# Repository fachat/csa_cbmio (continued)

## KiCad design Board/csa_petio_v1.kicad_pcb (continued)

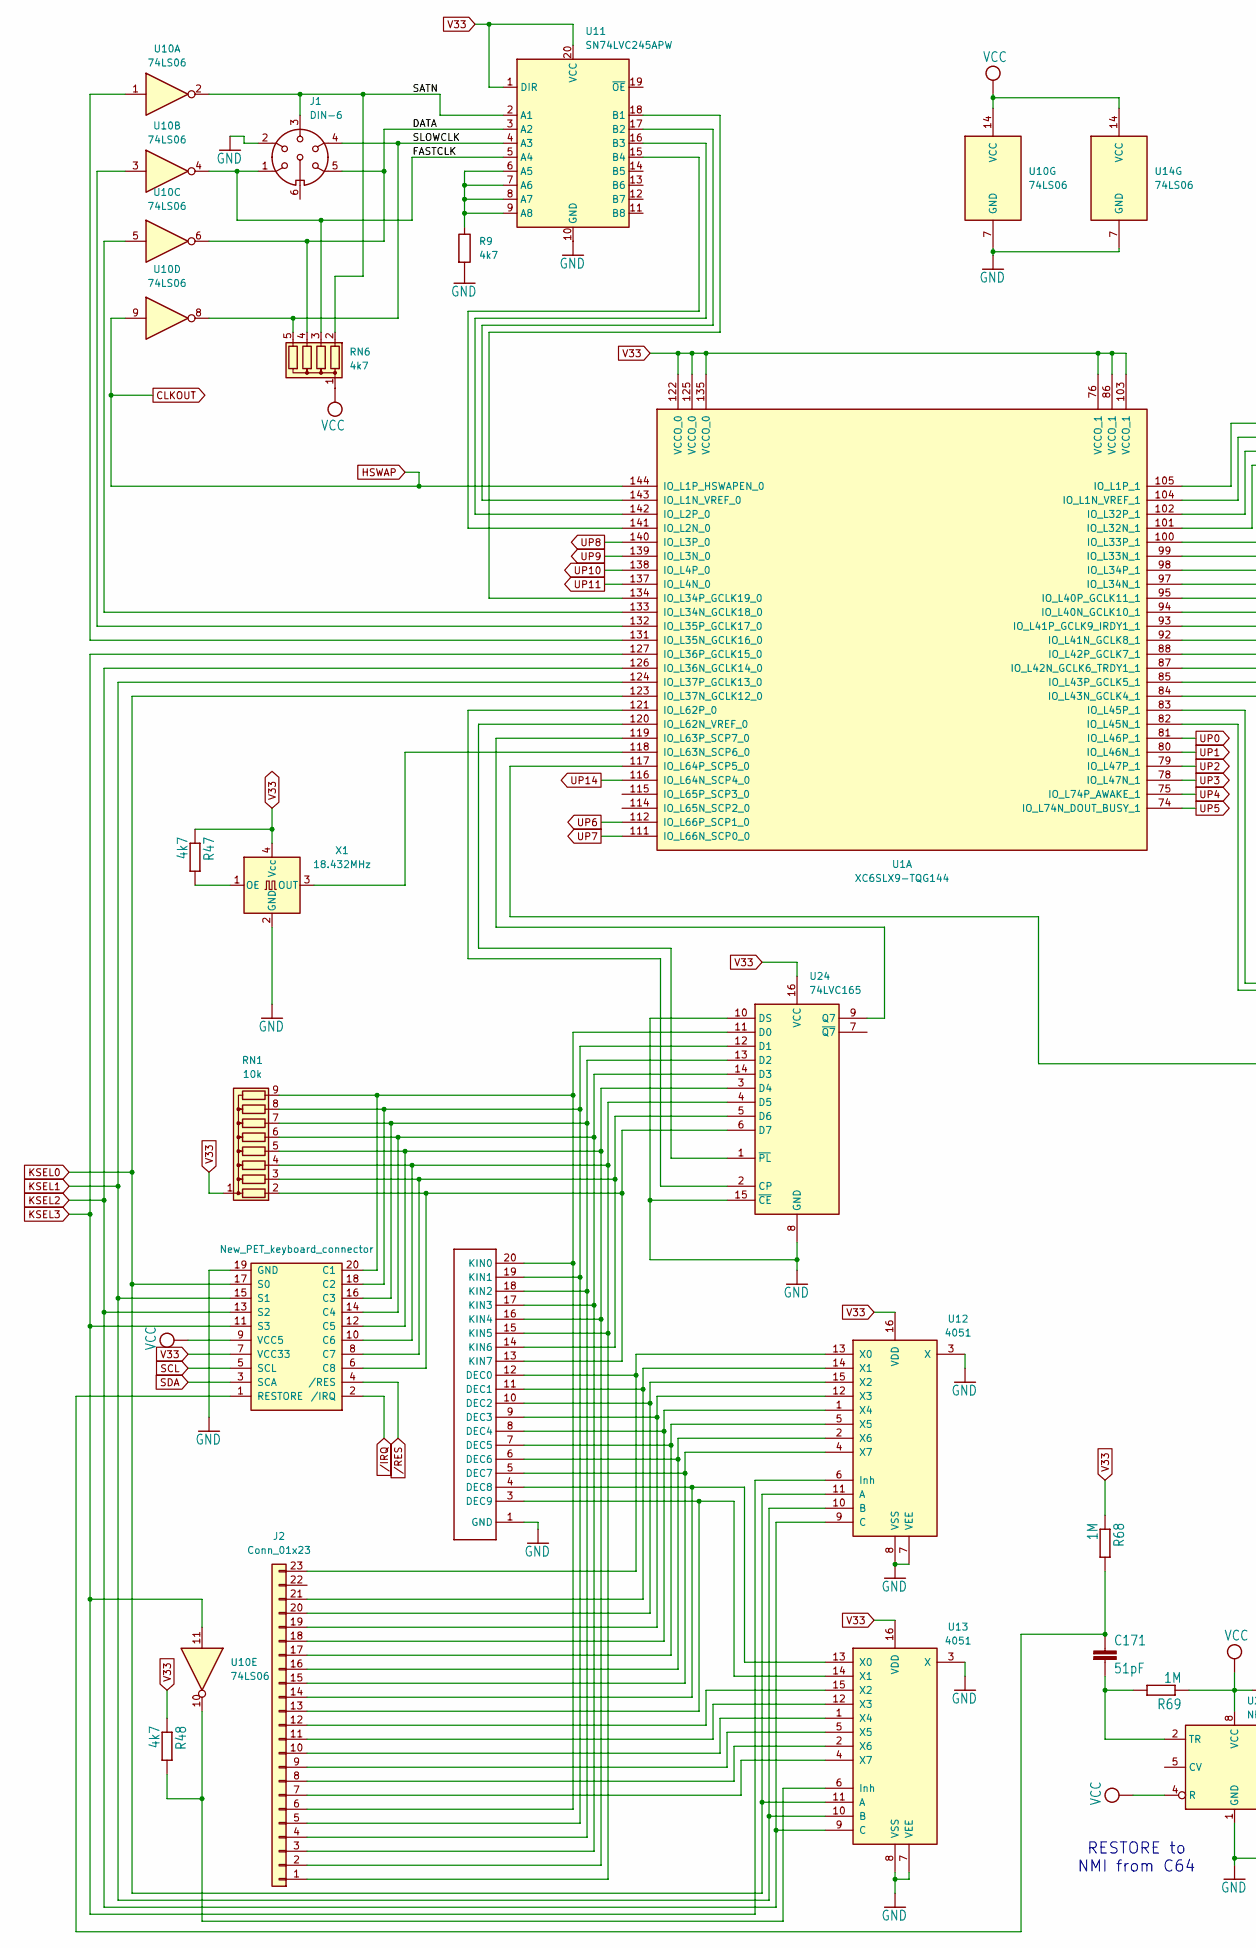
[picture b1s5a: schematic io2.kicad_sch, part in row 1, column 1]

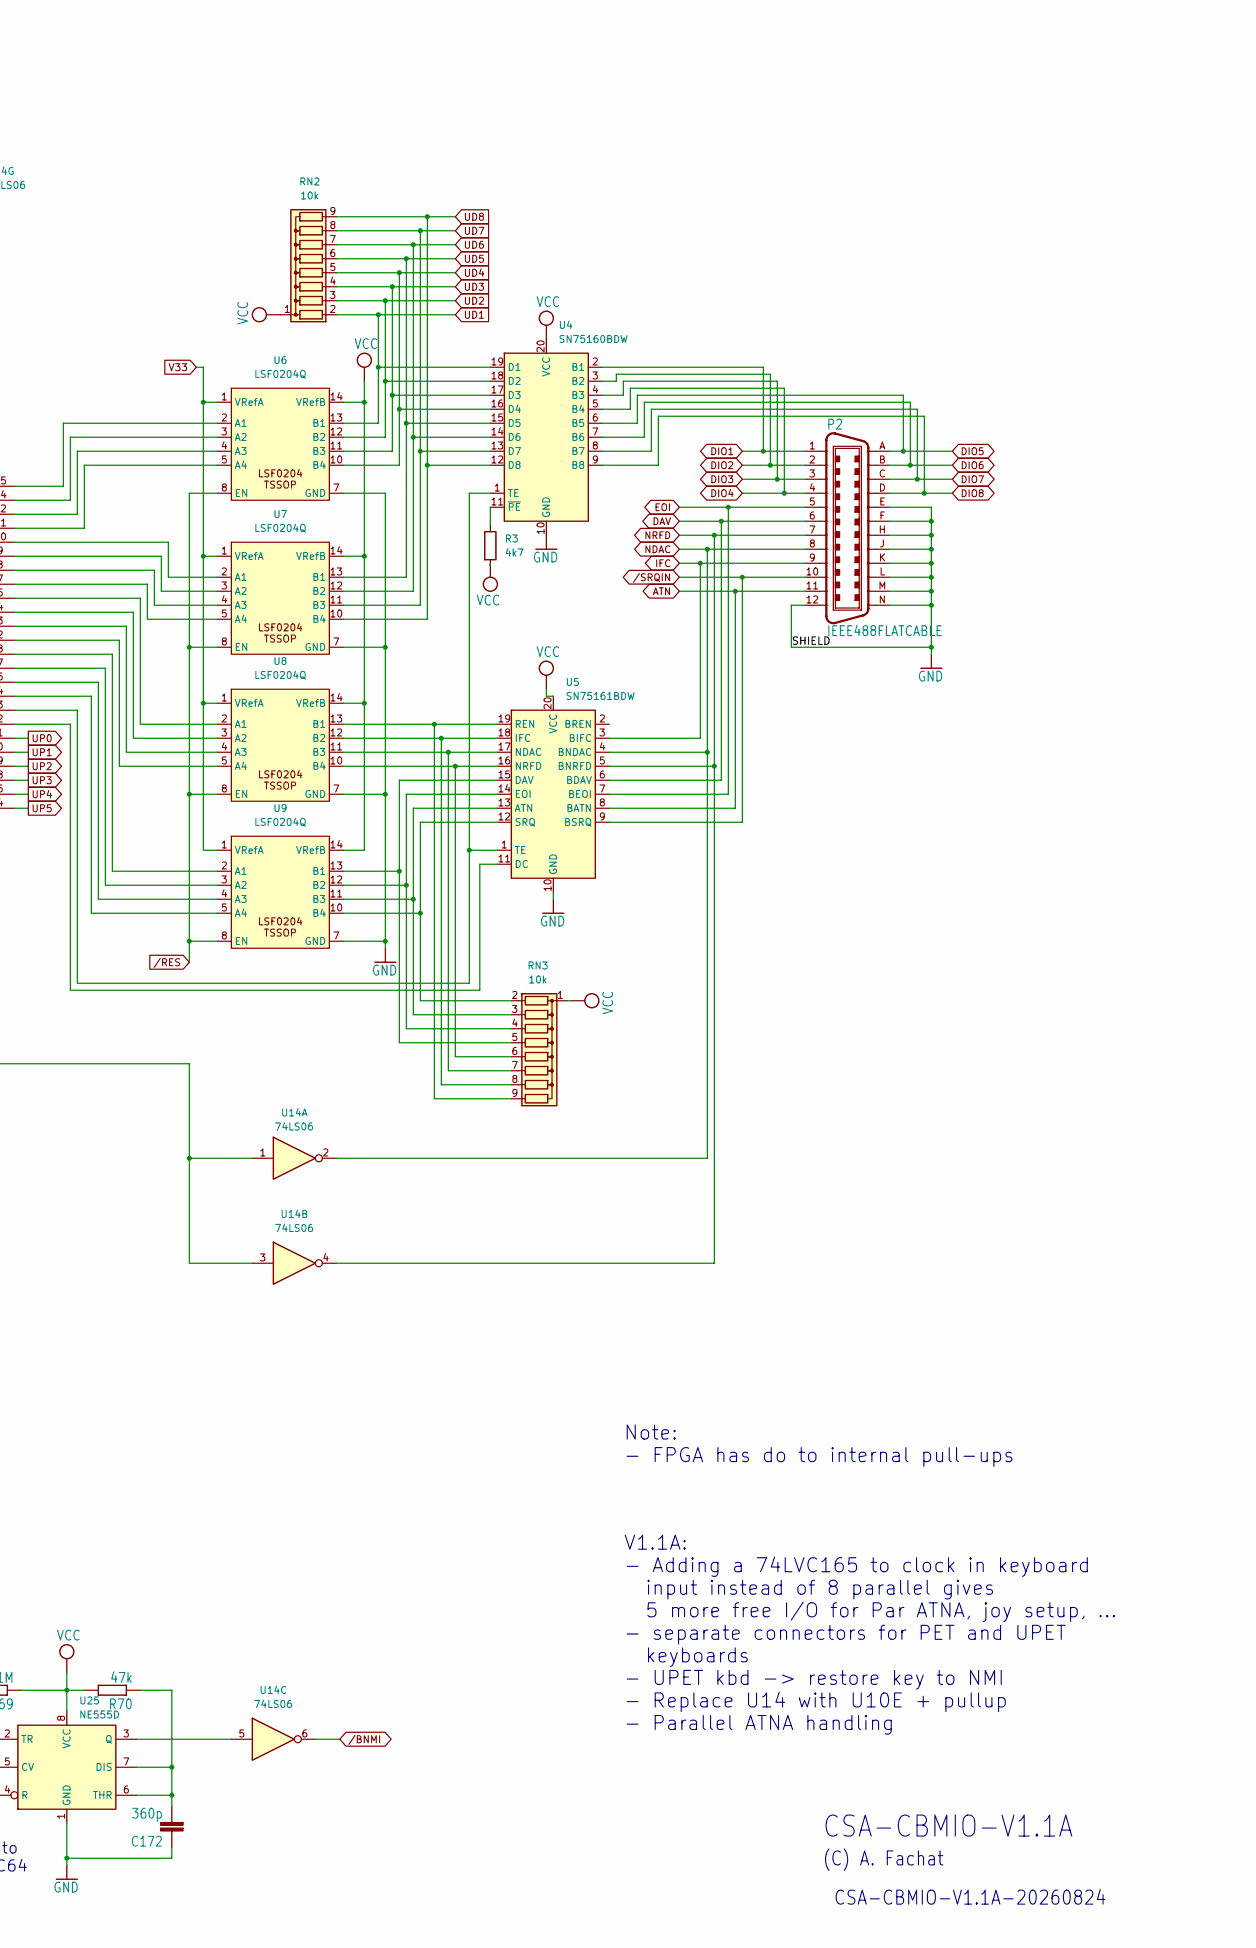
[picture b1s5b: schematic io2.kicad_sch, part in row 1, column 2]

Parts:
C171: 51pF; C_0805_2012Metric
C172: 360p; C_0805_2012Metric
J1: DIN-6; DIN6PIEC
J2: Conn_01x23; PinSocket_1x23_P2.54mm_Vertical
J3: New_PET_keyboard_connector; IDC-Header_2x10_P2.54mm_Vertical
P2: IEEE488FLATCABLE; FLAT24_IDC
P8: PinHeader_1x20_P2.54mm_Vertical
R3, R9, R47, R48: 4k7; R_0603_1608Metric_Pad0.98x0.95mm_HandSolder
R68, R69: 1M; R_0603_1608Metric_Pad0.98x0.95mm_HandSolder
R70: 47k; R_0603_1608Metric_Pad0.98x0.95mm_HandSolder
RN1, RN2, RN3: 10k; R_Array_SIP9
RN6: 4k7; R_Array_SIP5
U1: XC6SLX9-TQG144; TQFP-144_20x20mm_P0.5mm
U4: SN75160BDW; SOIC-20W_7.5x12.8mm_P1.27mm
U5: SN75161BDW; SOIC-20W_7.5x12.8mm_P1.27mm
U6, U7, U8, U9: LSF0204Q; TSSOP-14_4.4x5mm_P0.65mm
U10, U14: 74LS06; SO-14_3.9x8.65mm_P1.27mm
U11: SN74LVC245APW; TSSOP-20_4.4x6.5mm_P0.65mm
U12, U13: 4051; SOP-16_3.9x9.9mm_P1.27mm
U24: 74LVC165; TSSOP-16_4.4x5mm_P0.65mm
U25: NE555D; SOIC-8_3.9x4.9mm_P1.27mm
X1: 18.432MHz; Oscillator_SMD_SeikoEpson_SG8002CE-4Pin_3.2x2.5mm; LCSC C7434931

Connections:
/IO2/DATA: J1.5, RN6.4 (R3), U10.6, U11.3 (A2)
/IO2/FASTCLK: J1.1, RN6.3 (R2), U10.4, U11.5 (A4)
/IO2/SATN: J1.3, RN6.2 (R1), U10.2, U11.2 (A1)
/IO2/SLOWCLK: J1.4, RN6.5 (R4), U10.8, U11.4 (A3)
ATN: P2.11, U5.8 (BATN)
CLKOUT: U1.144 (IO_L1P_HSWAPEN_0), U10.9; also elsewhere on the board
DAV: P2.6, U5.6 (BDAV)
DIO1: P2.1, U4.2 (B1)
DIO2: P2.2, U4.3 (B2)
DIO3: P2.3, U4.4 (B3)
DIO4: P2.4, U4.5 (B4)
DIO5: P2.A (13), U4.6 (B5)
DIO6: P2.B (14), U4.7 (B6)
DIO7: P2.C (15), U4.8 (B7)
DIO8: P2.D (16), U4.9 (B8)
EOI: P2.5, U5.7 (BEOI); also elsewhere on the board
GND: C172.1, J1.2, J3.19 (GND), P2.12, P2.E (17), P2.F (18), P2.H (19), P2.J (20), P2.K (21), P2.L (22), P2.M (23), P2.N (24), P8.1 (GND), R9.2, U4.10 (GND), U5.10 (GND), U6.7 (GND), U7.7 (GND), U8.7 (GND), U9.7 (GND), U10.7 (GND), U11.10 (GND), U12.3 (X), U12.7 (VEE), U12.8 (VSS), U13.3 (X), U13.7 (VEE), U13.8 (VSS), U14.7 (GND), U24.8 (GND), U24.10 (DS), U24.15 (~CE), U25.1 (GND), X1.2 (GND); also elsewhere on the board
IFC: P2.9, U5.3 (BIFC)
KSEL0: J3.17 (S0), U1.123 (IO_L37N_GCLK12_0), U12.11 (A), U13.11 (A)
KSEL1: J3.15 (S1), U1.124 (IO_L37P_GCLK13_0), U12.10 (B), U13.10 (B)
KSEL2: J3.13 (S2), U1.126 (IO_L36N_GCLK14_0), U12.9 (C), U13.9 (C)
KSEL3: J3.11 (S3), U1.127 (IO_L36P_GCLK15_0), U10.11, U12.6 (Inh)
NDAC: P2.8, U5.4 (BNDAC), U14.2
NRFD: P2.7, U5.5 (BNRFD), U14.4
unnamed: J2.1, J3.10 (C6), P8.15 (KIN5), RN1.4 (R3), U24.4 (D5)
unnamed: J2.2, J3.12 (C5), P8.16 (KIN4), RN1.5 (R4), U24.3 (D4)
unnamed: J2.3, J3.14 (C4), P8.17 (KIN3), RN1.6 (R5), U24.14 (D3)
unnamed: J2.4, J3.16 (C3), P8.18 (KIN2), RN1.7 (R6), U24.13 (D2)
unnamed: J2.5, J3.18 (C2), P8.19 (KIN1), RN1.8 (R7), U24.12 (D1)
unnamed: J2.6, J3.20 (C1), P8.20 (KIN0), RN1.9 (R8), U24.11 (D0)
unnamed: J2.7, U13.4 (X7)
unnamed: J2.8, U13.2 (X6)
unnamed: J2.9, U13.5 (X5)
unnamed: J2.10, U13.1 (X4)
unnamed: J2.11, U13.12 (X3)
unnamed: J2.12, U13.15 (X2)
unnamed: J2.13, P8.3 (DEC9), U13.14 (X1)
unnamed: J2.14, P8.4 (DEC8), U13.13 (X0)
unnamed: J2.15, P8.5 (DEC7), U12.4 (X7)
unnamed: J2.16, P8.6 (DEC6), U12.2 (X6)
unnamed: J2.17, P8.7 (DEC5), U12.5 (X5)
unnamed: J2.18, P8.8 (DEC4), U12.1 (X4)
unnamed: J2.19, P8.9 (DEC3), U12.12 (X3)
unnamed: J2.20, P8.10 (DEC2), U12.15 (X2)
unnamed: J2.21, P8.11 (DEC1), U12.14 (X1)
unnamed: J2.23, P8.12 (DEC0), U12.13 (X0)
unnamed: J3.8 (C7), P8.14 (KIN6), RN1.3 (R2), U24.5 (D6)
unnamed: J3.6 (C8), P8.13 (KIN7), RN1.2 (R1), U24.6 (D7)
unnamed: C171.1, J3.1 (RESTORE), R68.2
unnamed: RN3.2 (R1), U5.12 (SRQ), U9.10 (B4)
unnamed: RN3.3 (R2), U5.13 (ATN), U9.11 (B3)
unnamed: RN3.4 (R3), U5.14 (EOI), U9.12 (B2)
unnamed: RN3.5 (R4), U5.15 (DAV), U9.13 (B1)
unnamed: RN3.6 (R5), U5.16 (NRFD), U8.10 (B4)
unnamed: RN3.7 (R6), U5.17 (NDAC), U8.11 (B3)
unnamed: RN3.8 (R7), U5.18 (IFC), U8.12 (B2)
unnamed: RN3.9 (R8), U5.19 (REN), U8.13 (B1)
unnamed: U1.104 (IO_L1N_VREF_1), U6.3 (A2)
unnamed: U1.105 (IO_L1P_1), U6.2 (A1)
unnamed: U1.101 (IO_L32N_1), U6.5 (A4)
unnamed: U1.102 (IO_L32P_1), U6.4 (A3)
unnamed: U1.99 (IO_L33N_1), U7.3 (A2)
unnamed: U1.100 (IO_L33P_1), U7.2 (A1)
unnamed: U1.97 (IO_L34N_1), U7.5 (A4)
unnamed: U1.133 (IO_L34N_GCLK18_0), U10.5
unnamed: U1.98 (IO_L34P_1), U7.4 (A3)
unnamed: U1.131 (IO_L35N_GCLK16_0), U10.1
unnamed: U1.132 (IO_L35P_GCLK17_0), U10.3
unnamed: U1.94 (IO_L40N_GCLK10_1), U8.3 (A2)
unnamed: U1.95 (IO_L40P_GCLK11_1), U8.2 (A1)
unnamed: U1.92 (IO_L41N_GCLK8_1), U8.5 (A4)
unnamed: U1.93 (IO_L41P_GCLK9_IRDY1_1), U8.4 (A3)
unnamed: U1.87 (IO_L42N_GCLK6_TRDY1_1), U9.3 (A2)
unnamed: U1.88 (IO_L42P_GCLK7_1), U9.2 (A1)
unnamed: U1.84 (IO_L43N_GCLK4_1), U9.5 (A4)
unnamed: U1.85 (IO_L43P_GCLK5_1), U9.4 (A3)
unnamed: U1.82 (IO_L45N_1), U5.11 (DC)
unnamed: U1.83 (IO_L45P_1), U4.1 (TE), U5.1 (TE)
unnamed: U1.120 (IO_L62N_VREF_0), U24.1 (~PL)
unnamed: U1.121 (IO_L62P_0), U24.2 (CP)
unnamed: U1.118 (IO_L63N_SCP6_0), X1.3 (OUT)
unnamed: U1.119 (IO_L63P_SCP7_0), U24.9 (Q7)
unnamed: U1.117 (IO_L64P_SCP5_0), U14.1, U14.3
unnamed: R3.1, U4.11 (~PE)
unnamed: R9.1, U11.6 (A5), U11.7 (A6), U11.8 (A7), U11.9 (A8)
unnamed: U1.134 (IO_L34P_GCLK19_0), U11.18 (B1)
unnamed: U1.143 (IO_L1N_VREF_0), U11.17 (B2)
unnamed: U1.142 (IO_L2P_0), U11.16 (B3)
unnamed: U1.141 (IO_L2N_0), U11.15 (B4)
unnamed: R48.2, U10.10, U13.6 (Inh)
unnamed: C172.2, R70.1, U25.6 (THR), U25.7 (DIS)
unnamed: U14.5, U25.3 (Q)
unnamed: C171.2, R69.2, U25.2 (TR)
unnamed: R47.2, X1.1 (OE)
SCL: J3.5 (SCL)
SDA: J3.3 (SCA)
UD1: RN2.2 (R1), U4.19 (D1), U6.13 (B1); also elsewhere on the board
UD2: RN2.3 (R2), U4.18 (D2), U6.12 (B2); also elsewhere on the board
UD3: RN2.4 (R3), U4.17 (D3), U6.11 (B3); also elsewhere on the board
UD4: RN2.5 (R4), U4.16 (D4), U6.10 (B4); also elsewhere on the board
UD5: RN2.6 (R5), U4.15 (D5), U7.13 (B1); also elsewhere on the board
UD6: RN2.7 (R6), U4.14 (D6), U7.12 (B2); also elsewhere on the board
UD7: RN2.8 (R7), U4.13 (D7), U7.11 (B3); also elsewhere on the board
UD8: RN2.9 (R8), U4.12 (D8), U7.10 (B4); also elsewhere on the board
UP0: U1.81 (IO_L46P_1); also elsewhere on the board
UP1: U1.80 (IO_L46N_1); also elsewhere on the board
UP2: U1.79 (IO_L47P_1); also elsewhere on the board
UP3: U1.78 (IO_L47N_1); also elsewhere on the board
UP4: U1.75 (IO_L74P_AWAKE_1); also elsewhere on the board
UP5: U1.74 (IO_L74N_DOUT_BUSY_1); also elsewhere on the board
UP6: U1.112 (IO_L66P_SCP1_0); also elsewhere on the board
UP7: U1.111 (IO_L66N_SCP0_0); also elsewhere on the board
UP8: U1.140 (IO_L3P_0); also elsewhere on the board
UP9: U1.139 (IO_L3N_0); also elsewhere on the board
UP10: U1.138 (IO_L4P_0); also elsewhere on the board
UP11: U1.137 (IO_L4N_0); also elsewhere on the board
UP14: U1.116 (IO_L64N_SCP4_0); also elsewhere on the board
V33: J3.7 (VCC33), R47.1, R48.1, R68.1, RN1.1 (common), U1.76 (VCCO_1), U1.86 (VCCO_1), U1.103 (VCCO_1), U1.122 (VCCO_0), U1.125 (VCCO_0), U1.135 (VCCO_0), U6.1 (VRefA), U7.1 (VRefA), U8.1 (VRefA), U9.1 (VRefA), U11.1 (DIR), U11.20 (VCC), U12.16 (VDD), U13.16 (VDD), U24.16 (VCC), X1.4 (Vcc); also elsewhere on the board
VCC: J3.9 (VCC5), R3.2, R69.1, R70.2, RN2.1 (common), RN3.1 (common), RN6.1 (common), U4.20 (VCC), U5.20 (VCC), U6.14 (VRefB), U7.14 (VRefB), U8.14 (VRefB), U9.14 (VRefB), U10.14 (VCC), U14.14 (VCC), U25.4 (R), U25.8 (VCC); also elsewhere on the board
/BNMI: U14.6; also elsewhere on the board
/IRQ: J3.2 (/IRQ); also elsewhere on the board
/RES: J3.4 (/RES), U6.8 (EN), U7.8 (EN), U8.8 (EN), U9.8 (EN); also elsewhere on the board

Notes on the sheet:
CSA-CBMIO-V1.1A
Note: - FPGA has do to internal pull-ups
CSA-CBMIO-V1.1A-20260824
RESTORE to NMI from C64
(C) A. Fachat
V1.1A: - Adding a 74LVC165 to clock in keyboard input instead of 8 parallel gives 5 more free I/O for Par ATNA, joy setup, ... - separate connectors for PET and UPET keyboards - UPET kbd -> restore key to NMI - Replace U14 with U10E + pullup - Parallel ATNA handling

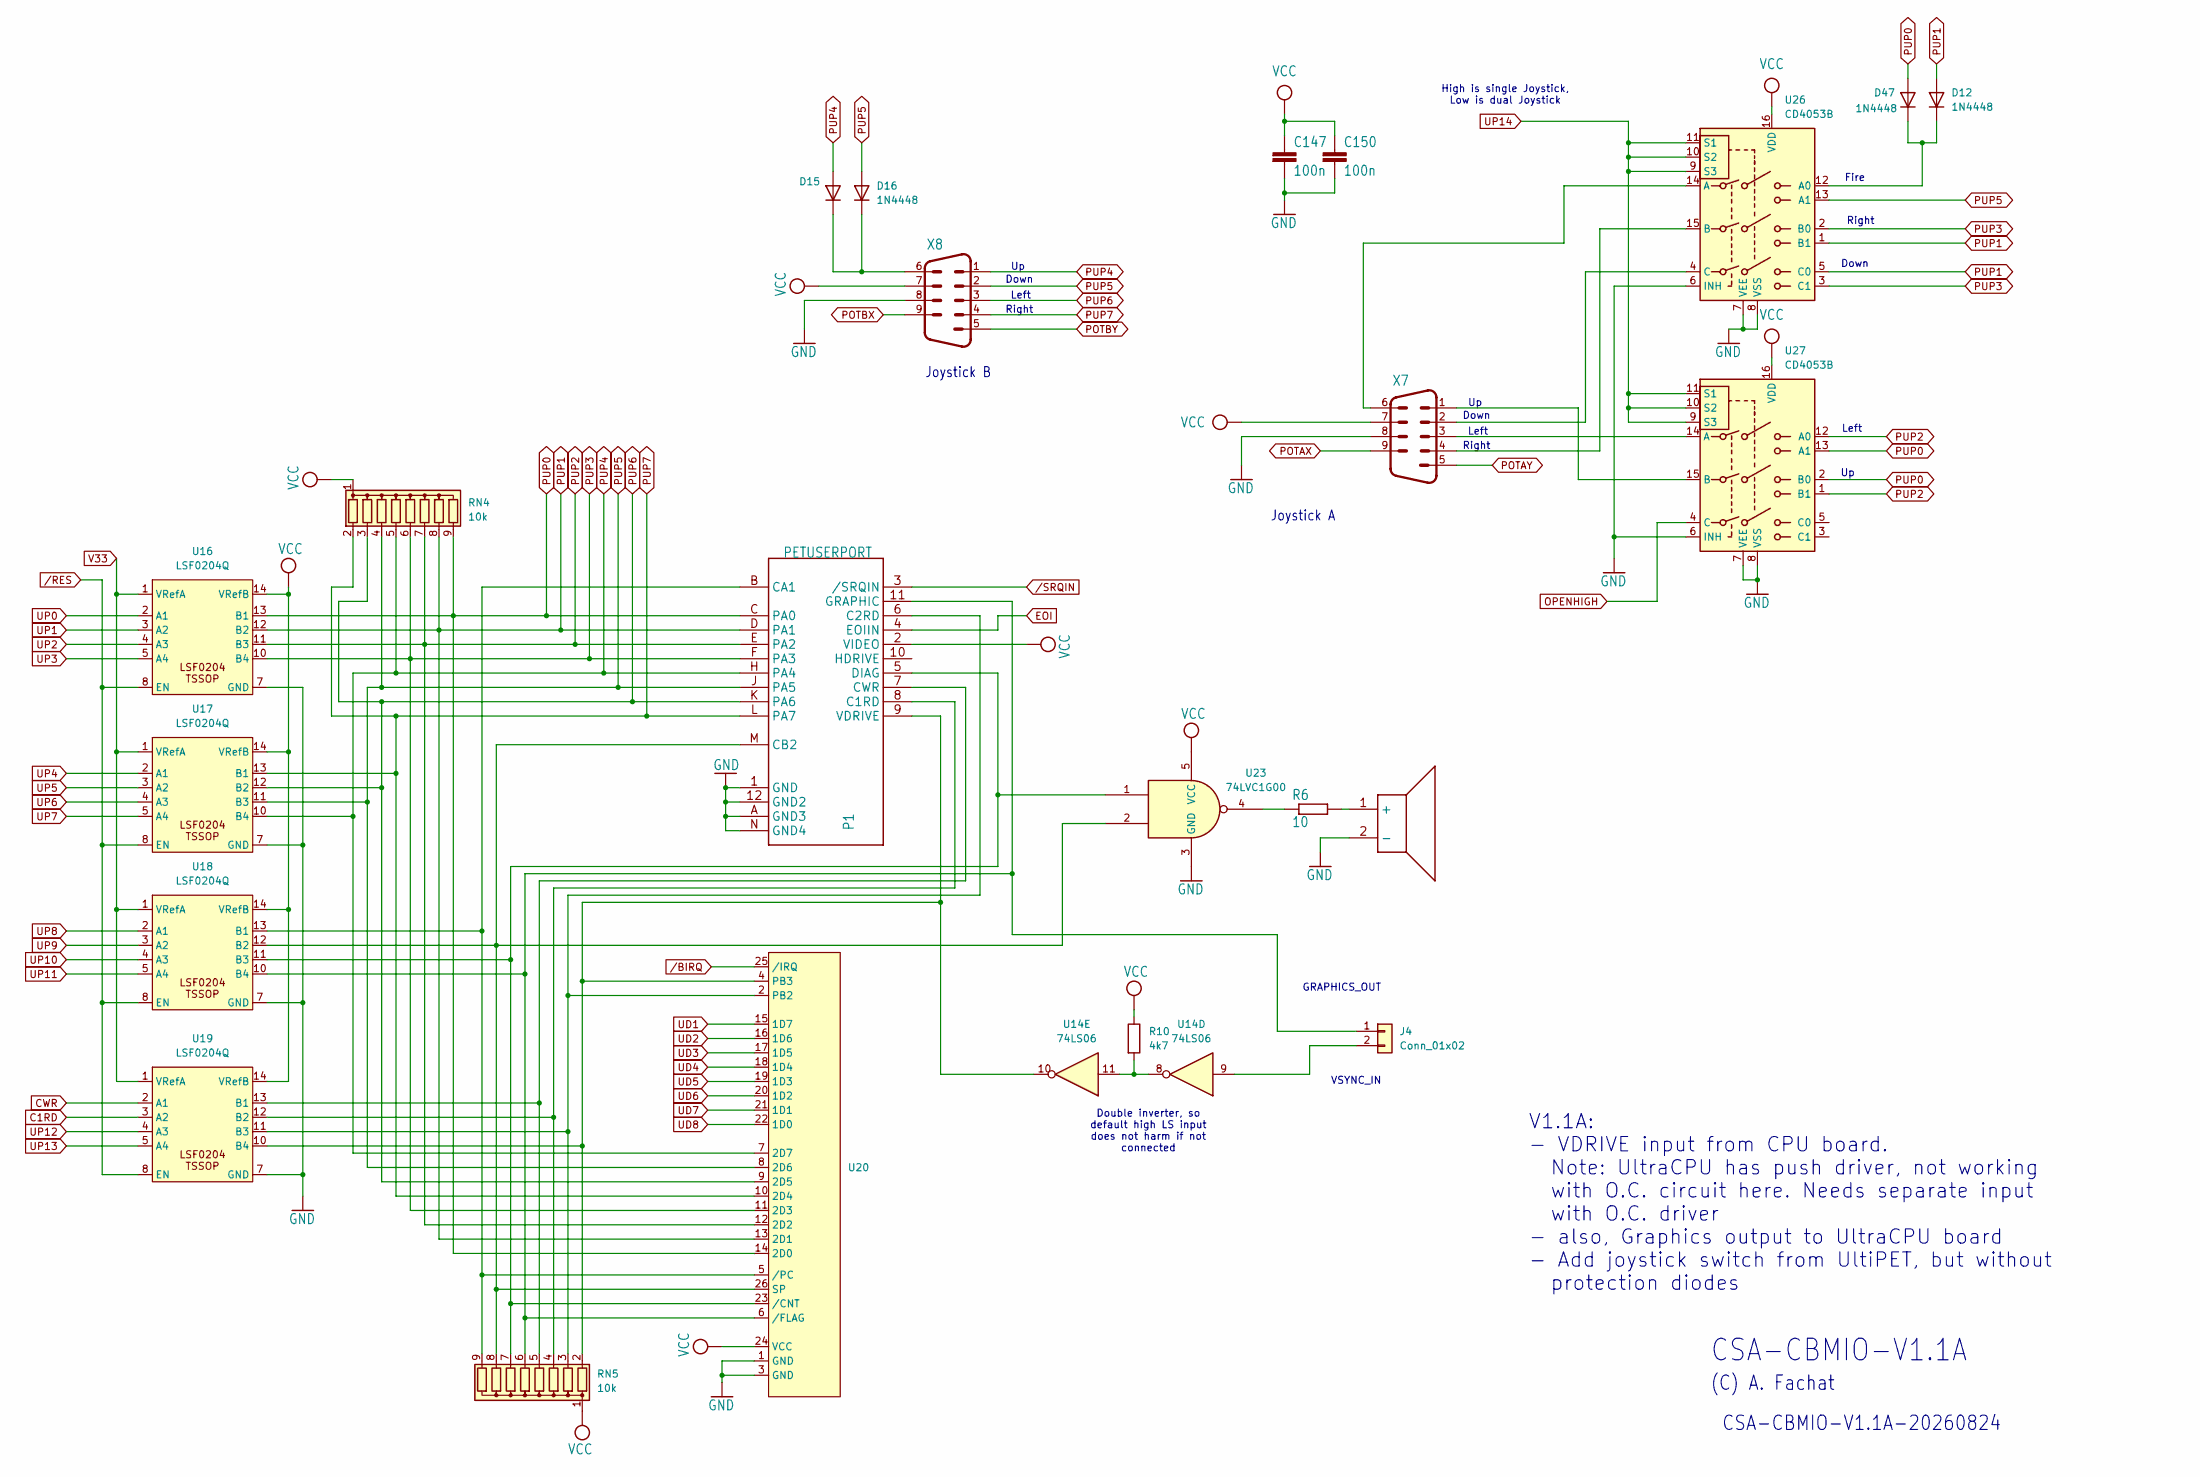
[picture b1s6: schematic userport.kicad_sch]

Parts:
BEEP1: PIEZOBEEPERPIEZO; MagneticBuzzer_StarMicronics_TMX-H
C147, C150: 100n; C_0805_2012Metric
D12, D15, D16, D47: 1N4448; D_SOD-123; LCSC C81598
J4: Conn_01x02; PinHeader_1x02_P2.54mm_Horizontal
P1: PETUSERPORT; FLAT24_IDC
R6: 10; 0207_10
R10: 4k7; R_0603_1608Metric_Pad0.98x0.95mm_HandSolder
RN4, RN5: 10k; R_Array_SIP9
U14: 74LS06; SO-14_3.9x8.65mm_P1.27mm
U16, U17, U18, U19: LSF0204Q; TSSOP-14_4.4x5mm_P0.65mm
U20: IDC-Header_2x13_P2.54mm_Vertical
U23: 74LVC1G00; SOT-353_SC-70-5_Handsoldering
U26, U27: CD4053B; SOIC-16_3.9x9.9mm_P1.27mm
X7, X8: M09-182; DSUB-9_Pins_Vertical_P2.77x2.84mm_MountingHoles; LCSC C189688

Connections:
C1RD: U19.3 (A2); also elsewhere on the board
CWR: U19.2 (A1); also elsewhere on the board
EOI: P1.4 (EOIIN); also elsewhere on the board
GND: BEEP1.2 (-), C147.2, C150.2, P1.1 (GND), P1.12 (GND2), P1.A (GND3), P1.N (GND4), U16.7 (GND), U17.7 (GND), U18.7 (GND), U19.7 (GND), U20.1 (GND), U20.3 (GND), U23.3 (GND), U26.6 (INH), U26.7 (VEE), U26.8 (VSS), U27.6 (INH), U27.7 (VEE), U27.8 (VSS), X7.8, X8.8; also elsewhere on the board
unnamed: BEEP1.1 (+), R6.2
unnamed: D12.1 (K), D47.1 (K), U26.12 (A0)
unnamed: D15.1 (K), D16.1 (K), X8.6
unnamed: J4.1, P1.11 (GRAPHIC), RN5.6 (R5), U18.10 (B4), U20.6 (/FLAG)
unnamed: J4.2, U14.9
unnamed: P1.8 (C1RD), RN5.4 (R3), U19.12 (B2)
unnamed: P1.6 (C2RD), RN5.3 (R2), U19.11 (B3), U20.2 (PB2)
unnamed: P1.B (CA1), RN5.9 (R8), U18.13 (B1), U20.5 (/PC)
unnamed: P1.M (CB2), RN5.8 (R7), U18.12 (B2), U20.26 (SP), U23.2
unnamed: P1.7 (CWR), RN5.5 (R4), U19.13 (B1)
unnamed: P1.5 (DIAG), RN5.7 (R6), U18.11 (B3), U20.23 (/CNT), U23.1
unnamed: P1.9 (VDRIVE), RN5.2 (R1), U14.10, U19.10 (B4), U20.4 (PB3)
unnamed: R6.1, U23.4
unnamed: R10.2, U14.8, U14.11
unnamed: U26.14 (A), X7.6
unnamed: U26.15 (B), X7.4
unnamed: U26.4 (C), X7.2
unnamed: U27.14 (A), X7.3
unnamed: U27.15 (B), X7.1
OPENHIGH: U27.4 (C)
POTAX: X7.9
POTAY: X7.5
POTBX: X8.9
POTBY: X8.5
PUP0: D47.2 (A), P1.C (PA0), RN4.9 (R8), U16.13 (B1), U20.14 (2D0), U27.2 (B0), U27.13 (A1)
PUP1: D12.2 (A), P1.D (PA1), RN4.8 (R7), U16.12 (B2), U20.13 (2D1), U26.1 (B1), U26.5 (C0)
PUP2: P1.E (PA2), RN4.7 (R6), U16.11 (B3), U20.12 (2D2), U27.1 (B1), U27.12 (A0)
PUP3: P1.F (PA3), RN4.6 (R5), U16.10 (B4), U20.11 (2D3), U26.2 (B0), U26.3 (C1)
PUP4: D15.2 (A), P1.H (PA4), RN4.5 (R4), U17.10 (B4), U20.7 (2D7), X8.1
PUP5: D16.2 (A), P1.J (PA5), RN4.4 (R3), U17.11 (B3), U20.8 (2D6), U26.13 (A1), X8.2
PUP6: P1.K (PA6), RN4.3 (R2), U17.12 (B2), U20.9 (2D5), X8.3
PUP7: P1.L (PA7), RN4.2 (R1), U17.13 (B1), U20.10 (2D4), X8.4
UD1: U20.15 (1D7); also elsewhere on the board
UD2: U20.16 (1D6); also elsewhere on the board
UD3: U20.17 (1D5); also elsewhere on the board
UD4: U20.18 (1D4); also elsewhere on the board
UD5: U20.19 (1D3); also elsewhere on the board
UD6: U20.20 (1D2); also elsewhere on the board
UD7: U20.21 (1D1); also elsewhere on the board
UD8: U20.22 (1D0); also elsewhere on the board
UP0: U16.2 (A1); also elsewhere on the board
UP1: U16.3 (A2); also elsewhere on the board
UP2: U16.4 (A3); also elsewhere on the board
UP3: U16.5 (A4); also elsewhere on the board
UP4: U17.2 (A1); also elsewhere on the board
UP5: U17.3 (A2); also elsewhere on the board
UP6: U17.4 (A3); also elsewhere on the board
UP7: U17.5 (A4); also elsewhere on the board
UP8: U18.2 (A1); also elsewhere on the board
UP9: U18.3 (A2); also elsewhere on the board
UP10: U18.4 (A3); also elsewhere on the board
UP11: U18.5 (A4); also elsewhere on the board
UP12: U19.4 (A3); also elsewhere on the board
UP13: U19.5 (A4); also elsewhere on the board
UP14: U26.9 (S3), U26.10 (S2), U26.11 (S1), U27.9 (S3), U27.10 (S2), U27.11 (S1); also elsewhere on the board
V33: U16.1 (VRefA), U17.1 (VRefA), U18.1 (VRefA), U19.1 (VRefA); also elsewhere on the board
VCC: C147.1, C150.1, P1.2 (VIDEO), R10.1, RN4.1 (common), RN5.1 (common), U16.14 (VRefB), U17.14 (VRefB), U18.14 (VRefB), U19.14 (VRefB), U20.24 (VCC), U23.5 (VCC), U26.16 (VDD), U27.16 (VDD), X7.7, X8.7; also elsewhere on the board
/BIRQ: U20.25 (/IRQ); also elsewhere on the board
/RES: U16.8 (EN), U17.8 (EN), U18.8 (EN), U19.8 (EN); also elsewhere on the board

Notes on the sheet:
Right
Left
GRAPHICS_OUT
V1.1A: - VDRIVE input from CPU board. Note: UltraCPU has push driver, not working with O.C. circuit here. Needs separate input with O.C. driver - also, Graphics output to UltraCPU board - Add joystick switch from UltiPET, but without protection diodes
Joystick B
Joystick A
CSA-CBMIO-V1.1A
Down
(C) A. Fachat
High is single Joystick, Low is dual Joystick
VSYNC_IN
Double inverter, so default high LS input does not harm if not connected
CSA-CBMIO-V1.1A-20260824
Fire

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
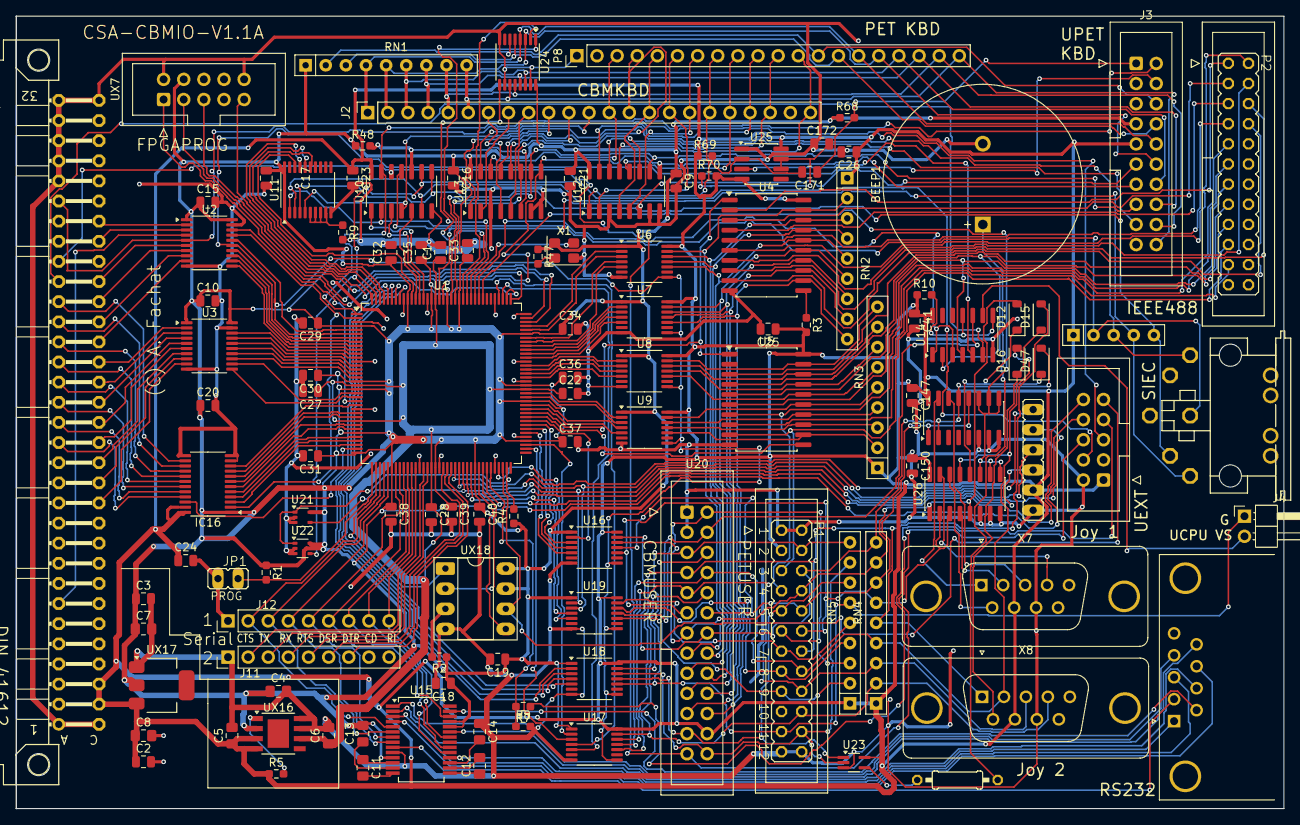
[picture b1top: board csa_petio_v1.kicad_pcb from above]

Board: 2 copper layers, 160.0 x 100.0 mm, 120 parts (0 on the bottom side), 247 nets.

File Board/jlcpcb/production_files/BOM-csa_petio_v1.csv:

Comment,Designator,Footprint,LCSC,Quantity
10,R6,0207_10,C2149605,1
100n,"C1,C10,C147,C15,C150,C16,C17,C18,C19,C2,C20,C21,C22,C23,C24,C25,C26,C27,C28,C29,C3,C30,C31,C32,C33,C34,C35,C36,C37,C38,C39,C40,C41,C9",C_0805_2012Metric,C49678,34
10k,R5,R_0603_1608Metric_Pad0.98x0.95mm_HandSolder,C25804,1
10k,"RN1,RN2,RN3,RN4,RN5",R_Array_SIP9,C8692,5
18.432MHz,X1,Oscillator_SMD_SeikoEpson_SG8002CE-4Pin_3.2x2.5mm,C7434931,1
1M,"R68,R69",R_0603_1608Metric_Pad0.98x0.95mm_HandSolder,C22935,2
1N4448,"D12,D15,D16,D47",D_SOD-123,C81598,4
1u,"C11,C12,C13,C14",C_0805_2012Metric_Pad1.18x1.45mm_HandSolder,C28323,4
22u,"C4,C5,C6,C7",C_0805_2012Metric_Pad1.18x1.45mm_HandSolder,C45783,4
330,"R2,R4,R7,R8",R_0603_1608Metric_Pad0.98x0.95mm_HandSolder,C23138,4
360p,C172,C_0805_2012Metric,C28167,1
4051,"U12,U13",SOP-16_3.9x9.9mm_P1.27mm,C507180,2
47k,R70,R_0603_1608Metric_Pad0.98x0.95mm_HandSolder,C25819,1
47u,C8,C_0805_2012Metric_Pad1.18x1.45mm_HandSolder,C16780,1
4k7,RN6,R_Array_SIP5,C11392,1
4k7,"R1,R10,R3,R47,R48,R9",R_0603_1608Metric_Pad0.98x0.95mm_HandSolder,C23162,6
51pF,C171,C_0805_2012Metric,C5375853,1
74LS06,"U10,U14",SO-14_3.9x8.65mm_P1.27mm,C513512,2
74LVC165,U24,TSSOP-16_4.4x5mm_P0.65mm,C41558098,1
74LVC1G00,U23,SOT-353_SC-70-5_Handsoldering,C8185,1
74LVC1G125,"U21,U22",SOT-353_SC-70-5,C12519,2
74LVC8T245SO24,IC16,TSSOP-24_4.4x7.8mm_P0.65mm,C27643,1
ADM560,U15,SSOP-28_5.3x10.2mm_P0.65mm,C658278,1
AP2132BB,UX16,Diodes_PSOP-8,C338874,1
CBMTAPE,P5,JP6,C492405,1
CD4053B,"U26,U27",SOIC-16_3.9x9.9mm_P1.27mm,C6742,2
CSABUS,P4,CSABUS,C5173362,1
Conn_01x02,J4,PinHeader_1x02_P2.54mm_Horizontal,C492410,1
Conn_01x09,"J11,J12",PinHeader_1x09_P2.54mm_Vertical,C492408,2
Conn_01x23,J2,PinSocket_1x23_P2.54mm_Vertical,C7430379,1
DIN-6,J1,DIN6PIEC,C54573054,1
IEEE488FLATCABLE,P2,FLAT24_IDC,C5157635,1
JP1E,JP1,JP1,C492401,1
LDI1117,UX17,SOT-223,C6186,1
LSF0204Q,"U16,U17,U18,U19,U6,U7,U8,U9",TSSOP-14_4.4x5mm_P0.65mm,C2677502,8
M09-182,"X7,X8",DSUB-9_Pins_Vertical_P2.77x2.84mm_MountingHoles,C189688,2
M09HPS,X3,DSUB-9_Pins_Horizontal_P2.77x2.84mm_EdgePinOffset9.90mm_Housed_MountingHolesOffset11.32mm,C19077344,1
NE555D,U25,SOIC-8_3.9x4.9mm_P1.27mm,C7593,1
New_PET_keyboard_connector,J3,IDC-Header_2x10_P2.54mm_Vertical,C3405,1
PETUSERPORT,P1,FLAT24_IDC,C5157635,1
SN74LVC245APW,"U11,U2,U3",TSSOP-20_4.4x6.5mm_P0.65mm,C7848,3
SN75160BDW,U4,SOIC-20W_7.5x12.8mm_P1.27mm,C882412,1
SN75161BDW,U5,SOIC-20W_7.5x12.8mm_P1.27mm,C2671348,1
SPIFLASH,UX18,DIP-8_W7.62mm_Socket_LongPads,C72124,1
XC6SLX9-TQG144,U1,TQFP-144_20x20mm_P0.5mm,C27408,1
XILINXPROG,UX7,IDC-Header_2x05_P2.54mm_Vertical,C5665,1
~,P8,PinHeader_1x20_P2.54mm_Vertical,C50981,1
~,P9,IDC-Header_2x05_P2.54mm_Vertical,C5665,1
~,U20,IDC-Header_2x13_P2.54mm_Vertical,C7501247,1

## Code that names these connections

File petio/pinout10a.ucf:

# bus

# phi2 is on a GCLK pin!
# required due to UART's use with too many non-clock resources
net phi2 			loc=p23 | iostandard=lvttl;
net phi2				bufg=clk | PERIOD=1000;
net phi2				clock_dedicated_route = false;

#INST "phi2_bufg" LOC = BUFGMUX_X2Y10;
#INST "phi2_ibufg_bufg.o" LOC = BUFGMUX_X2Y11;

net rwb				loc=p2 | iostandard=lvcmos33;
net niosel			loc=p5 | iostandard=lvcmos33;
net nres				loc=p6 | iostandard=lvcmos33;
net irq				loc=p1 | iostandard=lvcmos33;
net nbe				loc=p35 | iostandard=lvcmos33;

net a<0>				loc=p7 | iostandard=lvttl;
net a<1>				loc=p8 | iostandard=lvttl;
net a<2>				loc=p9 | iostandard=lvttl;
net a<3>				loc=p10 | iostandard=lvttl;
net a<4>				loc=p11 | iostandard=lvttl;
net a<5>				loc=p12 | iostandard=lvttl;
net a<6>				loc=p14 | iostandard=lvttl;
net a<7>				loc=p15 | iostandard=lvttl;
net a<8>				loc=p16 | iostandard=lvttl;
net a<9>				loc=p17 | iostandard=lvttl;
net a<10>			loc=p21 | iostandard=lvttl;
net a<11>			loc=p22 | iostandard=lvttl;

net d<0>				loc=p24 | iostandard=lvttl;
net d<1>				loc=p26 | iostandard=lvttl;
net d<2>				loc=p27 | iostandard=lvttl;
net d<3>				loc=p29 | iostandard=lvttl;
net d<4>				loc=p30 | iostandard=lvttl;
net d<5>				loc=p32 | iostandard=lvttl;
net d<6>				loc=p33 | iostandard=lvttl;
net d<7>				loc=p34 | iostandard=lvttl;

# serial (rs232)

net lcts				loc=p39 | iostandard=lvttl;
net lrts				loc=p43 | iostandard=lvttl;
net ltx				loc=p40 | iostandard=lvttl;
net lrx				loc=p41 | iostandard=lvttl;
net ldtr				loc=p45 | iostandard=lvttl;
net ldsr				loc=p44 | iostandard=lvttl;
net lri				loc=p47 | iostandard=lvttl;
net ldcd				loc=p46 | iostandard=lvttl;

net rcts				loc=p48 | iostandard=lvttl | pullup; # currently misused as config input
net rrts				loc=p55 | iostandard=lvttl;
net rtx				loc=p50 | iostandard=lvttl;
net rrx				loc=p51 | iostandard=lvttl | pullup;
net rdtr				loc=p57 | iostandard=lvttl;
net rdsr				loc=p56 | iostandard=lvttl;

# cassette

net c1sw				loc=p58	| iostandard=lvttl;
net cwr				loc=p60	| iostandard=lvttl;
net c1rd				loc=p59	| iostandard=lvttl;
net c1mtr			loc=p61	| iostandard=lvttl;

# SPI

net spiiosel		loc=p66	| iostandard=lvttl;
net spiclk			loc=p70	| iostandard=lvttl;
net spimiso			loc=p67	| iostandard=lvttl;
net spimosi			loc=p64	| iostandard=lvttl;

# serial IEC

net datain			loc=p143		| iostandard=lvttl;
net clkin			loc=p142		| iostandard=lvttl;
net satnin			loc=p134		| iostandard=lvttl;
net srqin			loc=p141		| iostandard=lvttl;

net dataout			loc=p133		| iostandard=lvttl;
net clkout			loc=p144		| iostandard=lvttl;
net satnout			loc=p131		| iostandard=lvttl;
net srqout			loc=p132		| iostandard=lvttl;

# keyboard

net ksel<0>			loc=p123		| iostandard=lvttl;
net ksel<1>			loc=p124		| iostandard=lvttl;
net ksel<2>			loc=p126		| iostandard=lvttl;
net ksel<3>			loc=p127		| iostandard=lvttl;

net kin<0>			loc=p121		| iostandard=lvttl;
net kin<1>			loc=p120		| iostandard=lvttl;
net kin<2>			loc=p119		| iostandard=lvttl;
net kin<3>			loc=p118		| iostandard=lvttl;
net kin<4>			loc=p117		| iostandard=lvttl;
net kin<5>			loc=p116		| iostandard=lvttl;
net kin<6>			loc=p115		| iostandard=lvttl;
net kin<7>			loc=p114		| iostandard=lvttl;

# IEEE488

net dio<0>			loc=p105		| iostandard=lvttl;
net dio<1>			loc=p104		| iostandard=lvttl;
net dio<2>			loc=p102		| iostandard=lvttl;
net dio<3>			loc=p101		| iostandard=lvttl;
net dio<4>			loc=p100		| iostandard=lvttl;
net dio<5>			loc=p99		| iostandard=lvttl;
net dio<6>			loc=p98		| iostandard=lvttl;
net dio<7>			loc=p97		| iostandard=lvttl;

net nrfd				loc=p92		| iostandard=lvttl;
net ndac				loc=p93		| iostandard=lvttl;
net dav				loc=p88		| iostandard=lvttl;
net eoi				loc=p87		| iostandard=lvttl;
net atn				loc=p85		| iostandard=lvttl;
net ifc				loc=p94		| iostandard=lvttl;
net ren				loc=p95		| iostandard=lvttl;
net psrq				loc=p84		| iostandard=lvttl;
net te				loc=p83		| iostandard=lvttl;
net dc				loc=p82		| iostandard=lvttl;


# userport

net up<0>			loc=p81	 | iostandard=lvttl;
net up<1>			loc=p80	 | iostandard=lvttl;
net up<2>			loc=p79	 | iostandard=lvttl;
net up<3>			loc=p78	 | iostandard=lvttl;
net up<4>			loc=p75	 | iostandard=lvttl;
net up<5>			loc=p74	 | iostandard=lvttl;
net up<6>			loc=p112	 | iostandard=lvttl;
net up<7>			loc=p111	 | iostandard=lvttl;
net up<8>			loc=p140	 | iostandard=lvttl;
net up<9>			loc=p139	 | iostandard=lvttl;
net up<10>			loc=p138	 | iostandard=lvttl;
net up<11>			loc=p137	 | iostandard=lvttl;
net up<12>			loc=p62	 | iostandard=lvttl;
net up<13>			loc=p69	 | iostandard=lvttl | pullup;

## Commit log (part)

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2025-08-14 adding keyboard, serial IEC
2025-08-14 add serial, SPI-10-5V
2025-08-14 schematics 1st full rev
2025-08-14 add schematics
2025-08-24 full connect, starting on prod
2025-08-24 fix version on PCB
2025-08-24 prod files
2025-08-24 prod files as submitted
2025-08-24 update PDF schematics
2026-01-31 initial Flash FPGA config
2026-01-31 io address select
2026-01-31 prep first pia for keyboard
2026-03-18 work on vhdl
2026-03-21 1st working as 1.0B
2026-03-21 add gitignore for work files
2026-03-21 pias show registers
2026-03-22 VIA compiles but untested
2026-03-23 integrate via1
2026-03-23 started detector for IEEE488 direction (to control 7516x chips)
2026-03-24 setting up IEEE488 bus direction control and I/O
2026-03-24 untangle transition timing for static via signals
2026-03-24 fixed some issues
2026-03-24 remove unused input
2026-03-24 refactored via Timer A
2026-03-25 refactor via tb and sr
2026-03-27 refactor via interrupt flags
2026-04-01 disable all ints for now; back to for testing; up13 with pullup
2026-04-03 use rcts as config input; pull to low for I/O page 8, 9 otherwise
2026-04-06 fix event clear triggers
2026-04-06 fix t1 starts
2026-04-06 cleanup, send pia1 cb1 input to debug out on rtx
2026-04-06 cleanup
2026-04-06 fix PIA CBx interrupt handling
2026-04-08 IEEE direction handling fixed
2026-04-08 introduce 2nd VIA and start serial IEC
2026-04-09 some IEC tries
2026-04-10 serial IEC works with slow mode
2026-04-10 still no fast mode
2026-04-11 add initial UART
